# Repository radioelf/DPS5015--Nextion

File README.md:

# Control twod DPS5015 - Nextion 
Codes for the control of two DPS5015 sources through to nextion screen.

Codigos para el control de dos fuentes DPS5015 a través de una pantalla nextion.

https://www.youtube.com/watch?v=COuCyDTJvEc

Creative Commons License Disclaimer

UNLESS OTHERWISE MUTUALLY AGREED TO BY THE PARTIES IN WRITING, LICENSOR OFFERS THE WORK AS-IS AND MAKES NO REPRESENTATIONS OR WARRANTIES OF ANY KIND CONCERNING THE WORK, EXPRESS, IMPLIED, STATUTORY OR OTHERWISE, INCLUDING, WITHOUT LIMITATION, WARRANTIES OF TITLE, MERCHANTIBILITY, FITNESS FOR A PARTICULAR PURPOSE, NONINFRINGEMENT, OR THE ABSENCE OF LATENT OR OTHER DEFECTS, ACCURACY, OR THE PRESENCE OF ABSENCE OF ERRORS, WHETHER OR NOT DISCOVERABLE. SOME JURISDICTIONS DO NOT ALLOW THE EXCLUSION OF IMPLIED WARRANTIES, SO SUCH EXCLUSION MAY NOT APPLY TO YOU. EXCEPT TO THE EXTENT REQUIRED BY APPLICABLE LAW, IN NO EVENT WILL LICENSOR BE LIABLE TO YOU ON ANY LEGAL THEORY FOR ANY SPECIAL, INCIDENTAL, CONSEQUENTIAL, PUNITIVE OR EXEMPLARY DAMAGES ARISING OUT OF THIS LICENSE OR THE USE OF THE WORK, EVEN IF LICENSOR HAS BEEN ADVISED OF THE POSSIBILITY OF SUCH DAMAGES.

http://creativecommons.org/licenses/by-sa/3.0/

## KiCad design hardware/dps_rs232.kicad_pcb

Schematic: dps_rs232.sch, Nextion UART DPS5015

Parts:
A1: Arduino_Nano
BZ1: Buzzer; Buzzer_12x9.5RM7.6
C1, C2, C3: 10nF; C_0603_1608Metric
C4: 100nF; C_0603_1608Metric
MK1: +5v; TestPoint_THTPad_D2.0mm_Drill1.0mm
MK2: GND; TestPoint_THTPad_D2.0mm_Drill1.0mm
MK3: A; TestPoint_THTPad_D2.0mm_Drill1.0mm
MK4: RX->nextion; TestPoint_THTPad_D2.0mm_Drill1.0mm
MK5: B; TestPoint_THTPad_D2.0mm_Drill1.0mm
MK6: TX<-nextion; TestPoint_THTPad_D2.0mm_Drill1.0mm
MK7: C; TestPoint_THTPad_D2.0mm_Drill1.0mm
MK8: ON_OFF_encoder; TestPoint_THTPad_D2.0mm_Drill1.0mm
MK9: USB_PC; TestPoint_THTPad_D2.0mm_Drill1.0mm
MK10, MK11: RX; TestPoint_THTPad_D2.0mm_Drill1.0mm
MK12: TX1; TestPoint_THTPad_D2.0mm_Drill1.0mm
MK13: TX2; TestPoint_THTPad_D2.0mm_Drill1.0mm
MK14: ON_3v3-5v; TestPoint_THTPad_D2.0mm_Drill1.0mm
MK15: Led2; TestPoint_THTPad_D2.0mm_Drill1.0mm
MK16: Led1; TestPoint_THTPad_D2.0mm_Drill1.0mm
Q1: Q_PNP; SOT-23
R1, R2, R3, R5, R6: 10K; R_0603_1608Metric
R4, R8, R9: 330R; R_0603_1608Metric
R7: 1K; R_0603_1608Metric
U1: 74HC126; SOIC-14_3.9x8.7mm_P1.27mm

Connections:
+5v: A1.27 (+5V), BZ1.1, C4.2, MK1.1, U1.14
/A: A1.5 (D2), C1.2, R1.1
/B: A1.6 (D3), C2.2, R2.1
/Buzzer: A1.9 (D6), R7.2
/C: A1.7 (D4), C3.2, R3.1
/Ledfuente1: A1.20 (A1), R4.2
/Ledfuente2: A1.8 (D5), R9.2
/ON_3v3-5v: A1.15 (D12), MK14.1
/ON_DPS1: A1.10 (D7), R5.1, U1.1, U1.10
/ON_DPS2: A1.11 (D8), R6.1, U1.4, U1.13
/ON_encoder: A1.12 (D9), MK8.1
/RX1: A1.2 (D0/RX), U1.8, U1.11
/RX2: A1.13 (D10), MK6.1
/TX1: A1.1 (D1/TX), U1.2, U1.5
/TX2: A1.14 (D11), R8.2
/USB_PC: A1.19 (A0), MK9.1
GND: A1.4 (GND), A1.29 (GND), C1.1, C2.1, C3.1, C4.1, MK2.1, Q1.2, R5.2, R6.2, U1.7
unnamed: BZ1.2, Q1.3
unnamed: MK3.1, R1.2
unnamed: MK4.1, R8.1
unnamed: MK5.1, R2.2
unnamed: MK7.1, R3.2
unnamed: MK15.1, R4.1
unnamed: MK16.1, R9.1
unnamed: Q1.1, R7.1
RX->DPS1: MK10.1, U1.3
RX->DPS2: MK11.1, U1.6
TX<-DPS1: MK12.1, U1.9
TX<-DPS2: MK13.1, U1.12

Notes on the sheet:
Encoder
Module: XL7015 DC-DC 5-80V

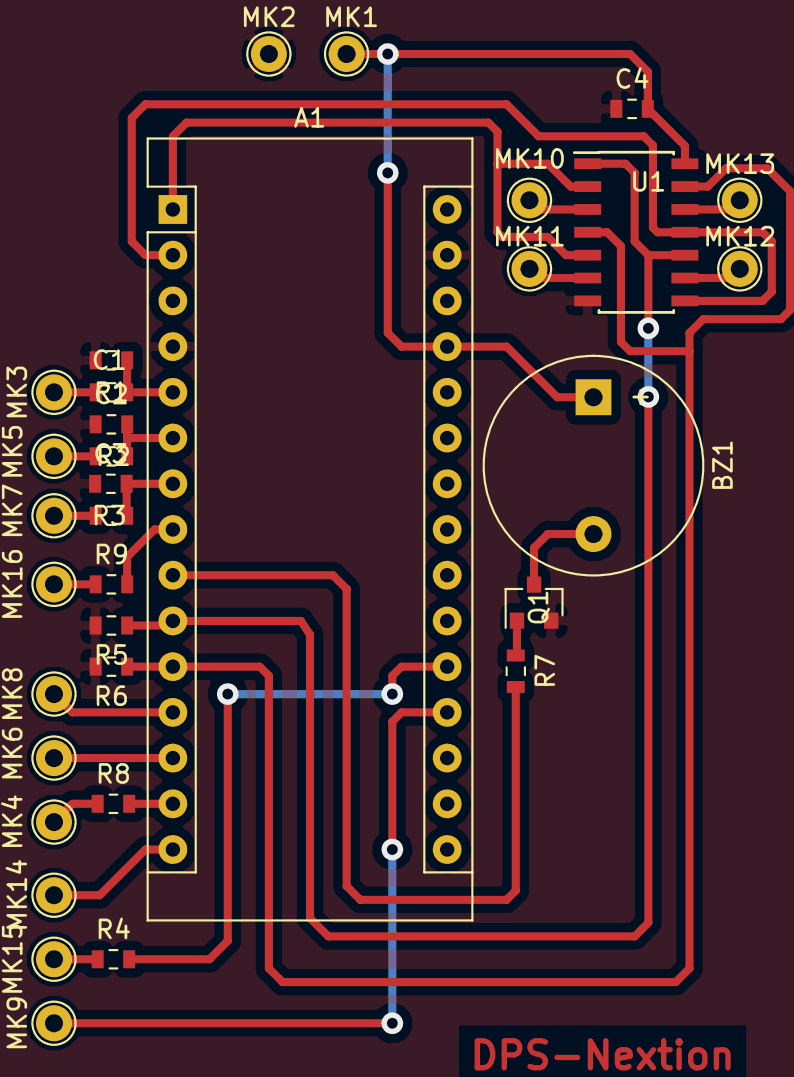
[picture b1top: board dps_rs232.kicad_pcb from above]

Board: 2 copper layers, 33 parts (0 on the bottom side), 29 nets.

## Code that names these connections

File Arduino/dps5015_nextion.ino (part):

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#define ENCODE_B 3
#define PULSADOR_PIN 4                                                      // pin pulsador encoder
#define LED_F1_PIN 5
#define BUZZER_PIN 6                 
//#define ON_DPS1  7                                                        // pin control TX/RX fuente 1 (74HC126)
//#define ON_DPS2  8                                                        // pin control TX/RX fuente 2 (74HC126)
#define ON_encoder  9                                                       // pin habilitación encoder (habilitado->0)
//RX->10 nextion
//TX->11 nextion
#define ON_5_3v3 12
#define LED_PIN 13                                                          // led pcb nano
#define USB_PC_PIN A0                                                       // pin 14 indica selección control por PC A0 (USB)
#define LED_F2_PIN 15

bool pc_control =0;
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  Serial.setTimeout(2000);                                                  // máximo en milisegundos de espera para la lectura a 2 segundos
  pinMode(10, INPUT);                                                       // pin 10 RX puerto 1
  pinMode(11, OUTPUT);                                                      // pin 11 TX puerto 1
  pinMode(USB_PC_PIN,INPUT);
  pinMode(BUZZER_PIN, OUTPUT);
  pinMode(LED_PIN, OUTPUT);
  pinMode(LED_F1_PIN, OUTPUT);
  pinMode(LED_F2_PIN, OUTPUT);
  pinMode(ON_DPS1, OUTPUT);
  pinMode(ON_DPS2, OUTPUT);
  pinMode(ON_encoder, OUTPUT);
  pinMode(ON_5_3v3, OUTPUT);
  pinMode(PULSADOR_PIN, INPUT_PULLUP);
  pinMode(ENCODE_A, INPUT_PULLUP);
  pinMode(ENCODE_B, INPUT_PULLUP);
  
  digitalWrite(ON_encoder, HIGH);                                           // OFF encoder
  digitalWrite(BUZZER_PIN, LOW);                                            
  digitalWrite(LED_PIN, LOW);
  digitalWrite(LED_F1_PIN, LOW);
  digitalWrite(LED_F2_PIN, LOW);
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  
  delay (500);                                                                                                       
  ini_nextion();
  if (analogRead(USB_PC_PIN) >500){                                         // comprobamos si tenemos el modo de control por PC
    digitalWrite(ON_5_3v3, LOW);
    txt_nextion("32", "Control  USB");
    cmd_nextion("tsw 255,0");
    dim_nextion();
    digitalWrite(ON_DPS2, LOW);
    digitalWrite(ON_DPS1, LOW);   
    while (analogRead(USB_PC_PIN) >500){
      delay (250);                                                          // esperamos que se pase a control por nextion
    }                                      
    digitalWrite(ON_5_3v3, HIGH);
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  }
  // para continuar tenemos que tener el bloqueo teclado de la fuentes a ON->1
  while (datos_RX_DPS[3] !=1 || status_RX_DPS ==255){                         // el valor de la respuesta se encuentra en la posición 3
    digitalWrite(BUZZER_PIN , HIGH);
    digitalWrite(LED_F1_PIN , HIGH);
    delay (500);
    digitalWrite(BUZZER_PIN , LOW);
    digitalWrite(LED_F1_PIN , LOW);
    delay (3000);
  }
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  }
  // para continuar tenemos que tener el bloqueo teclado a ON->1
  while (datos_RX_DPS[3] !=1 || status_RX_DPS ==255){                         // el valor de la respuesta se encuentra en la posición 3
    digitalWrite(BUZZER_PIN , HIGH);
    digitalWrite(LED_F2_PIN , HIGH);
    delay (150);
    digitalWrite(BUZZER_PIN , LOW);
    digitalWrite(LED_F2_PIN , LOW);
    delay (100);
    digitalWrite(BUZZER_PIN , HIGH);
    digitalWrite(LED_F2_PIN , HIGH);
    delay (150);
    digitalWrite(BUZZER_PIN , LOW);
    digitalWrite(LED_F2_PIN , LOW);
    delay (3000);
  }
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    }
    digitalWrite(LED_F1_PIN, fuente1_run);
    digitalWrite(LED_F2_PIN, fuente2_run);
    if (analogRead(USB_PC_PIN) >500){ 
      if (pc_control ==0){
        digitalWrite(ON_5_3v3, LOW);
        dim_nextion();
        control_pc(1);                                                        // bloqueamos pantalla, control por PC remoto
        while (analogRead(USB_PC_PIN) >500){                                  // esperamos que se pase a control por nextion
          delay (250);
        }
        digitalWrite(ON_5_3v3, HIGH);
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
// OFF zumbador
void buzzer_OFF(){
  digitalWrite(BUZZER_PIN, LOW);
  Timer1.stop();
}
// ON zumbador
void buzzer_ON(unsigned long run_buzzer){
  if (!on_off_buzzer) return;
  digitalWrite(BUZZER_PIN, HIGH);
  Timer1.setPeriod(run_buzzer);                                               // ajuntamos en microsegundos 
}

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
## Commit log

2018-05-18 Ini 18/5/18
